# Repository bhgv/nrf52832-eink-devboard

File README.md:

designed mainly for custom nrf52832 (E73-2G4M04S1B module) + e-Ink screen based
smart-clock 

Eagle CAD PCB in the /pcb folder

tested with 2 and 4 colors waveshare/goodisplay SPI e-Incs: 2.7", 2.3", 2.9". glass based & flexible

software part (IAR 7.7) with drivers for flexible e-ink 2.9" partially refresh (no black screens between drawings/refreshes), 
graphics, font, etc.
yet it is experimental.

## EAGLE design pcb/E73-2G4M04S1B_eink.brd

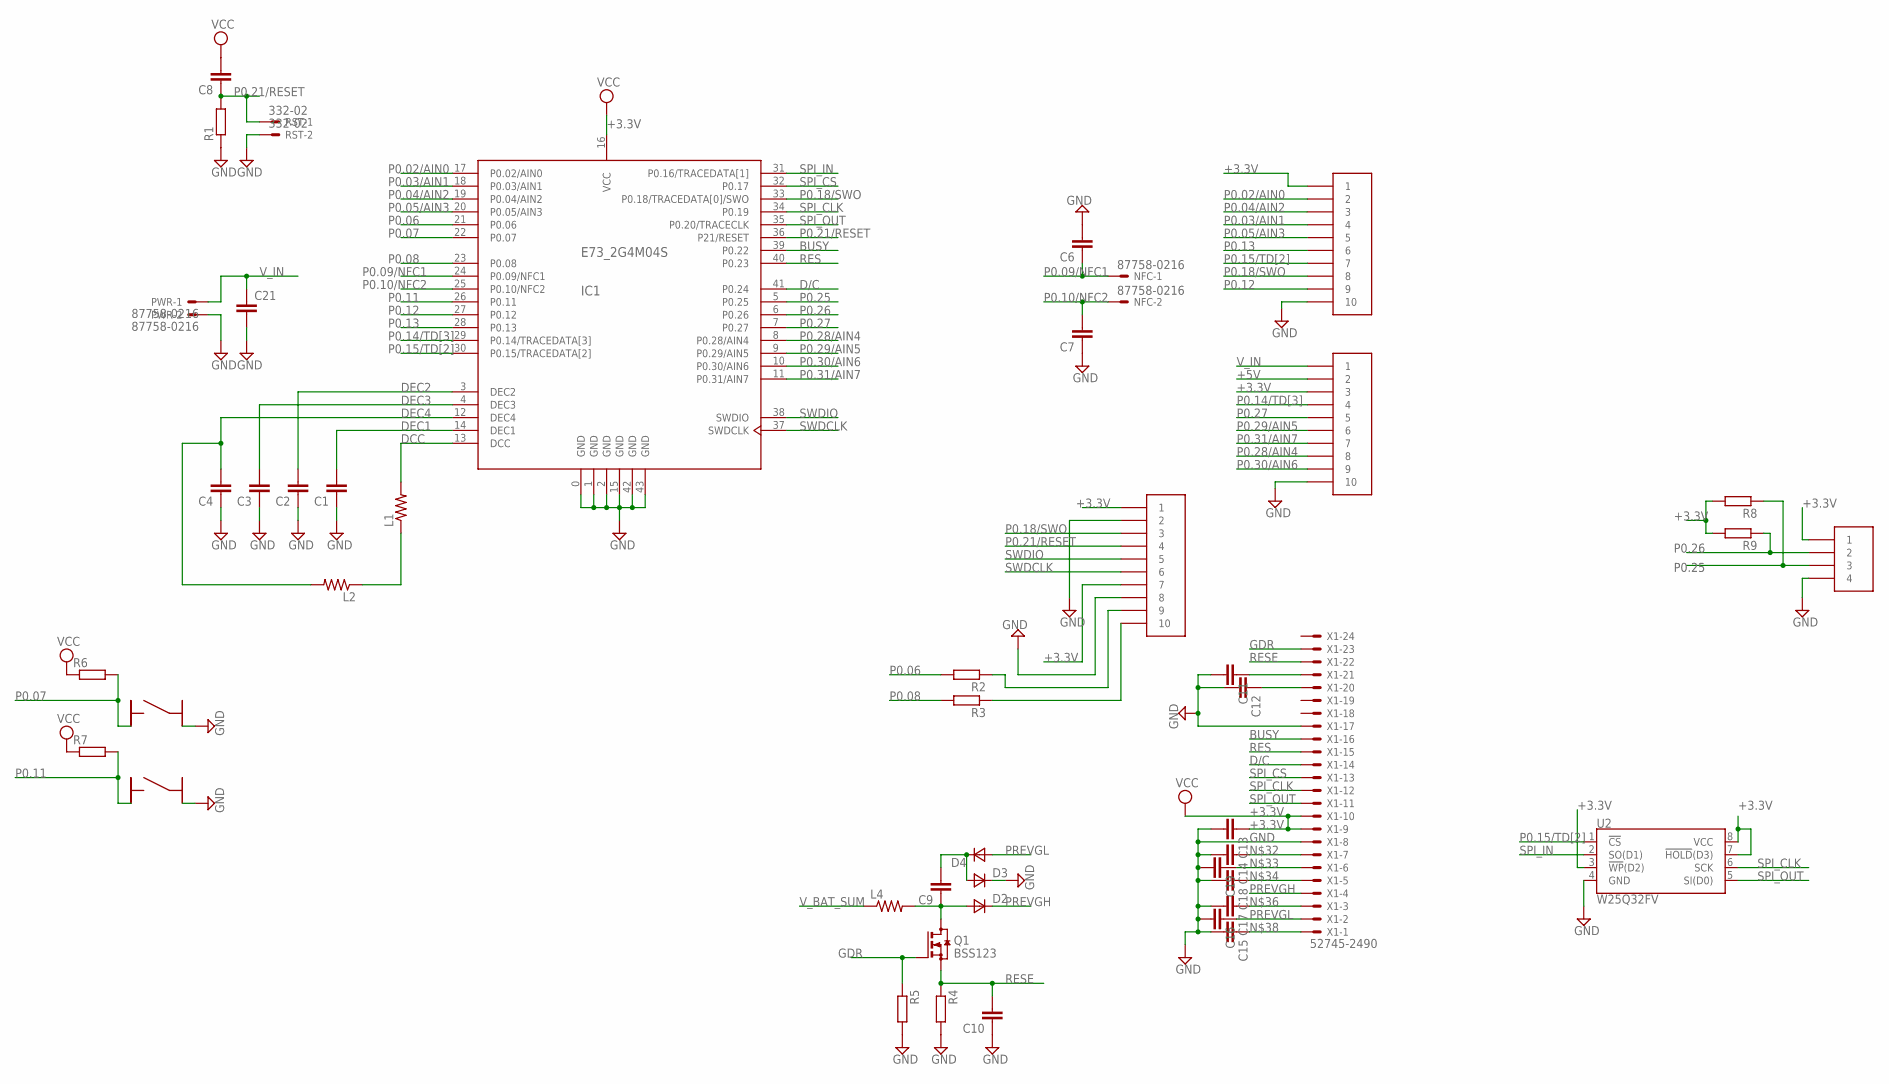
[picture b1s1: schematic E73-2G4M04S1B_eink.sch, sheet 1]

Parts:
C1, C2, C3, C4, C6, C7, C8, C9, C10, C11, C12, C13, C14, C15, C16, C17, C18, C19: C-EUC0603; C0603
C21: C-EUC0805; C0805
D2, D3, D4: DSOD323; SOD323
DBG-COM, DBG-COM1, DBG-COM2: HDR-1.27MM-110; HDR-1.27MM-1*10
IC1: E73_2G4M04S
L1, L2, L4: R-US_R0805; R0805
NFC: 87758-0216
PWR: 87758-0216
Q1: BSS123; SOT23
R1, R2, R3, R4, R5, R6, R7, R8, R9: R-EU_R0603; R0603
RST: 332-02
U2: W25Q32FV; SOIC-8
U$3: HDR-1.27MM-14; HDR-1.27MM-1*4
U$4, U$5: BUTTON_3X3MM_4PINS; BUT_3X3_4PINS
X1: 52745-2490

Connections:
+3.3V: C8.2, C13.1, DBG-COM.P$1 (1), DBG-COM.P$7 (7), DBG-COM1.P$1 (1), DBG-COM2.P$3 (3), IC1.16 (VCC), R6.1, R7.1, R8.2, R9.2, U2.3 (!WP!(D2)), U2.7 (!HOLD!(D3)), U2.8 (VCC), U$3.P$1 (1), X1.9, X1.10; also elsewhere on the board
+5V: DBG-COM2.P$2 (2); also elsewhere on the board
BUSY: IC1.39 (P0.22), X1.16
D/C: IC1.41 (P0.24), X1.14
DCC: IC1.13 (DCC), L1.2
DEC1: C1.2, IC1.14 (DEC1)
DEC2: C2.2, IC1.3 (DEC2)
DEC3: C3.2, IC1.4 (DEC3)
DEC4: C4.2, IC1.12 (DEC4), L2.2
GDR: Q1.1 (G), R5.1, X1.23
GND: C1.1, C2.1, C3.1, C4.1, C6.2, C7.1, C10.1, C11.2, C12.2, C13.2, C14.2, C15.2, C16.2, C17.2, C18.2, C19.2, C21.2, D3.1 (C), DBG-COM.P$2 (2), DBG-COM.P$8 (8), DBG-COM1.P$10 (10), DBG-COM2.P$10 (10), IC1.0 (GND), IC1.1 (GND), IC1.2 (GND), IC1.15 (GND), IC1.42 (GND), IC1.43 (GND), PWR.2, R1.1, R4.2, R5.2, RST.2, U2.4 (GND), U$3.P$4 (4), U$4.P$2, U$5.P$2, X1.8, X1.17; also elsewhere on the board
unnamed: DBG-COM.P$10 (10), R3.1
unnamed: L1.1, L2.1
unnamed: DBG-COM.P$9 (9), R2.1
unnamed: C9.1, D2.2 (A), L4.2, Q1.3 (D)
unnamed: C9.2, D3.2 (A), D4.1 (C)
unnamed: C11.1, X1.21
unnamed: C12.1, X1.20
unnamed: C14.1, X1.7
unnamed: C19.1, X1.6
unnamed: C18.1, X1.5
unnamed: C17.1, X1.3
unnamed: C15.1, X1.1
P0.02/AIN0: DBG-COM1.P$2 (2), IC1.17 (P0.02/AIN0)
P0.03/AIN1: DBG-COM1.P$4 (4), IC1.18 (P0.03/AIN1)
P0.04/AIN2: DBG-COM1.P$3 (3), IC1.19 (P0.04/AIN2)
P0.05/AIN3: DBG-COM1.P$5 (5), IC1.20 (P0.05/AIN3)
P0.06: IC1.21 (P0.06), R2.2
P0.07: IC1.22 (P0.07), R6.2, U$4.P$1
P0.08: IC1.23 (P0.08), R3.2
P0.09/NFC1: C6.1, IC1.24 (P0.09/NFC1), NFC.1
P0.10/NFC2: C7.2, IC1.25 (P0.10/NFC2), NFC.2
P0.11: IC1.26 (P0.11), R7.2, U$5.P$1
P0.12: DBG-COM1.P$9 (9), IC1.27 (P0.12)
P0.13: DBG-COM1.P$6 (6), IC1.28 (P0.13)
P0.14/TD[3]: DBG-COM2.P$4 (4), IC1.29 (P0.14/TRACEDATA[3])
P0.15/TD[2]: DBG-COM1.P$7 (7), IC1.30 (P0.15/TRACEDATA[2]), U2.1 (!CS!)
P0.18/SWO: DBG-COM.P$3 (3), DBG-COM1.P$8 (8), IC1.33 (P0.18/TRACEDATA[0]/SWO)
P0.21/RESET: C8.1, DBG-COM.P$4 (4), IC1.36 (P21/RESET), R1.2, RST.1
P0.25: IC1.5 (P0.25), R8.1, U$3.P$3 (3)
P0.26: IC1.6 (P0.26), R9.1, U$3.P$2 (2)
P0.27: DBG-COM2.P$5 (5), IC1.7 (P0.27)
P0.28/AIN4: DBG-COM2.P$8 (8), IC1.8 (P0.28/AIN4)
P0.29/AIN5: DBG-COM2.P$6 (6), IC1.9 (P0.29/AIN5)
P0.30/AIN6: DBG-COM2.P$9 (9), IC1.10 (P0.30/AIN6)
P0.31/AIN7: DBG-COM2.P$7 (7), IC1.11 (P0.31/AIN7)
PREVGH: D2.1 (C), X1.4
PREVGL: C16.1, D4.2 (A), X1.2
RES: IC1.40 (P0.23), X1.15
RESE: C10.2, Q1.2 (S), R4.1, X1.22
SPI_CLK: IC1.34 (P0.19), U2.6 (SCK), X1.12
SPI_CS: IC1.32 (P0.17), X1.13
SPI_IN: IC1.31 (P0.16/TRACEDATA[1]), U2.2 (SO(D1))
SPI_OUT: IC1.35 (P0.20/TRACECLK), U2.5 (SI(D0)), X1.11
SWDCLK: DBG-COM.P$6 (6), IC1.37 (SWDCLK)
SWDIO: DBG-COM.P$5 (5), IC1.38 (SWDIO)
V_BAT_SUM: L4.1; also elsewhere on the board
V_IN: C21.1, DBG-COM2.P$1 (1), PWR.1; also elsewhere on the board

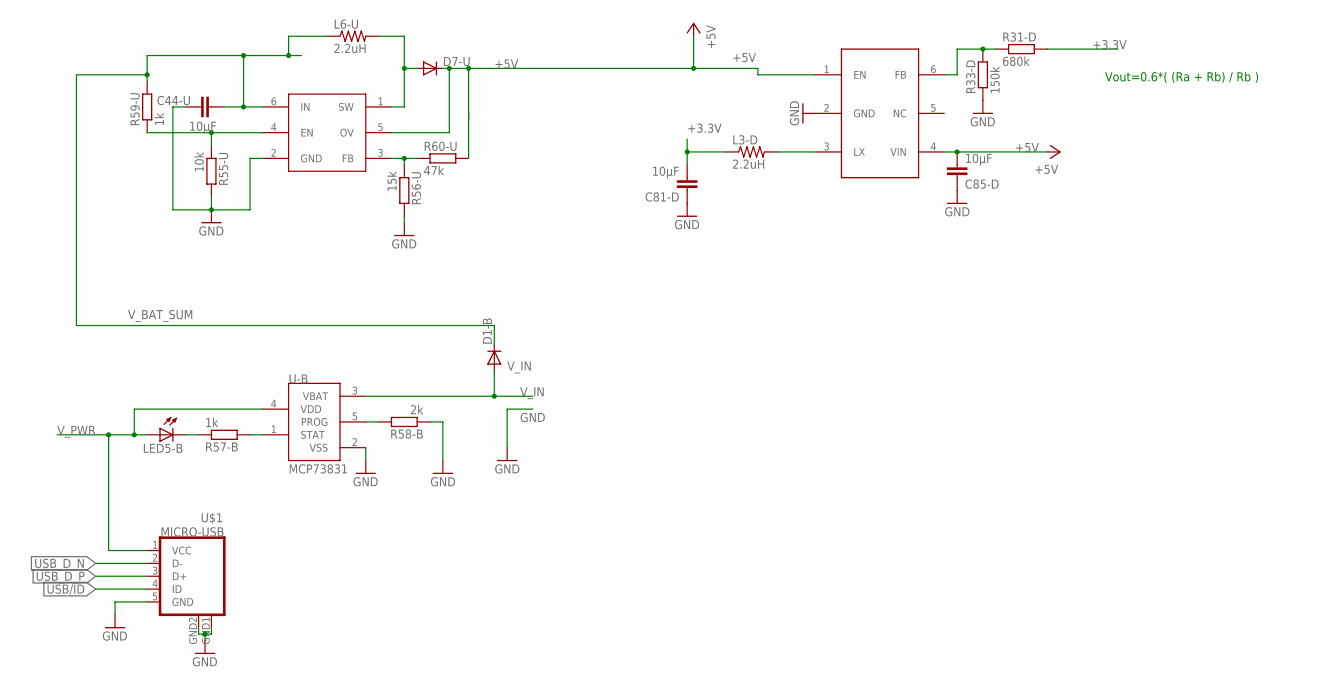
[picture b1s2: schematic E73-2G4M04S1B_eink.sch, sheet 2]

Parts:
C44-U, C81-D, C85-D: 10µF; C0805
D1-B, D7-U: DIODE-SOD323-W; SOD323-W
L3-D, L6-U: 2.2uH; R0805
LED5-B: LEDCHIPLED_0805; CHIPLED_0805
R31-D: 680k; R0603
R33-D: 150k; R0603
R55-U: 10k; R0603
R56-U: 15k; R0603
R57-B, R59-U: 1k; R0603
R58-B: 2k; R0603
R60-U: 47k; R0603
U$1: MICRO-USB
U-B: MCP73831; SOT23-5L
U-D: STI3411; SOT23-6
U-U: PT4101; SOT23-6

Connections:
+3.3V: C81-D.2, L3-D.1, R31-D.2; also elsewhere on the board
+5V: C85-D.2, D7-U.C, R60-U.2, U-D.1 (EN), U-D.4 (VIN), U-U.5 (OV); also elsewhere on the board
GND: C44-U.2, C81-D.1, C85-D.1, R33-D.1, R55-U.2, R56-U.2, R58-B.1, U$1.5 (GND), U$1.GND1 (GND), U$1.GND2 (GND), U-B.2 (VSS), U-D.2 (GND), U-U.2 (GND); also elsewhere on the board
unnamed: R56-U.1, R60-U.1, U-U.3 (FB)
unnamed: R55-U.1, R59-U.1, U-U.4 (EN)
unnamed: D7-U.A, L6-U.2, U-U.1 (SW)
unnamed: L3-D.2, U-D.3 (LX)
unnamed: R31-D.1, R33-D.2, U-D.6 (FB)
unnamed: R58-B.2, U-B.5 (PROG)
unnamed: R57-B.2, U-B.1 (STAT)
unnamed: LED5-B.C, R57-B.1
USB/ID: U$1.4 (ID)
USB_D_N: U$1.2 (D-)
USB_D_P: U$1.3 (D+)
V_BAT_SUM: C44-U.1, D1-B.C, L6-U.1, R59-U.2, U-U.6 (IN); also elsewhere on the board
V_IN: D1-B.A, U-B.3 (VBAT); also elsewhere on the board
V_PWR: LED5-B.A, U$1.1 (VCC), U-B.4 (VDD)

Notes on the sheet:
Vout=0.6*( (Ra + Rb) / Rb )

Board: 2 copper layers, 67 parts (48 on the bottom side), 67 nets, no tracks yet.

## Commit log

2020-05-22 added software part (IAR). drivers for eink 2.9" flex. partially refresh. it is experimental
2020-05-22 edited readme.md

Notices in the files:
parts and their libraries:
SparkFun-IC-Memory: Licensing: Creative Commons ShareAlike 4.0 International - https://creativecommons.org/licenses/by-sa/4.0
